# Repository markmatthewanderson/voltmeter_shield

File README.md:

# voltmeter_shield
 Voltmeter shield to be used with Arduino Uno.
 ....swag

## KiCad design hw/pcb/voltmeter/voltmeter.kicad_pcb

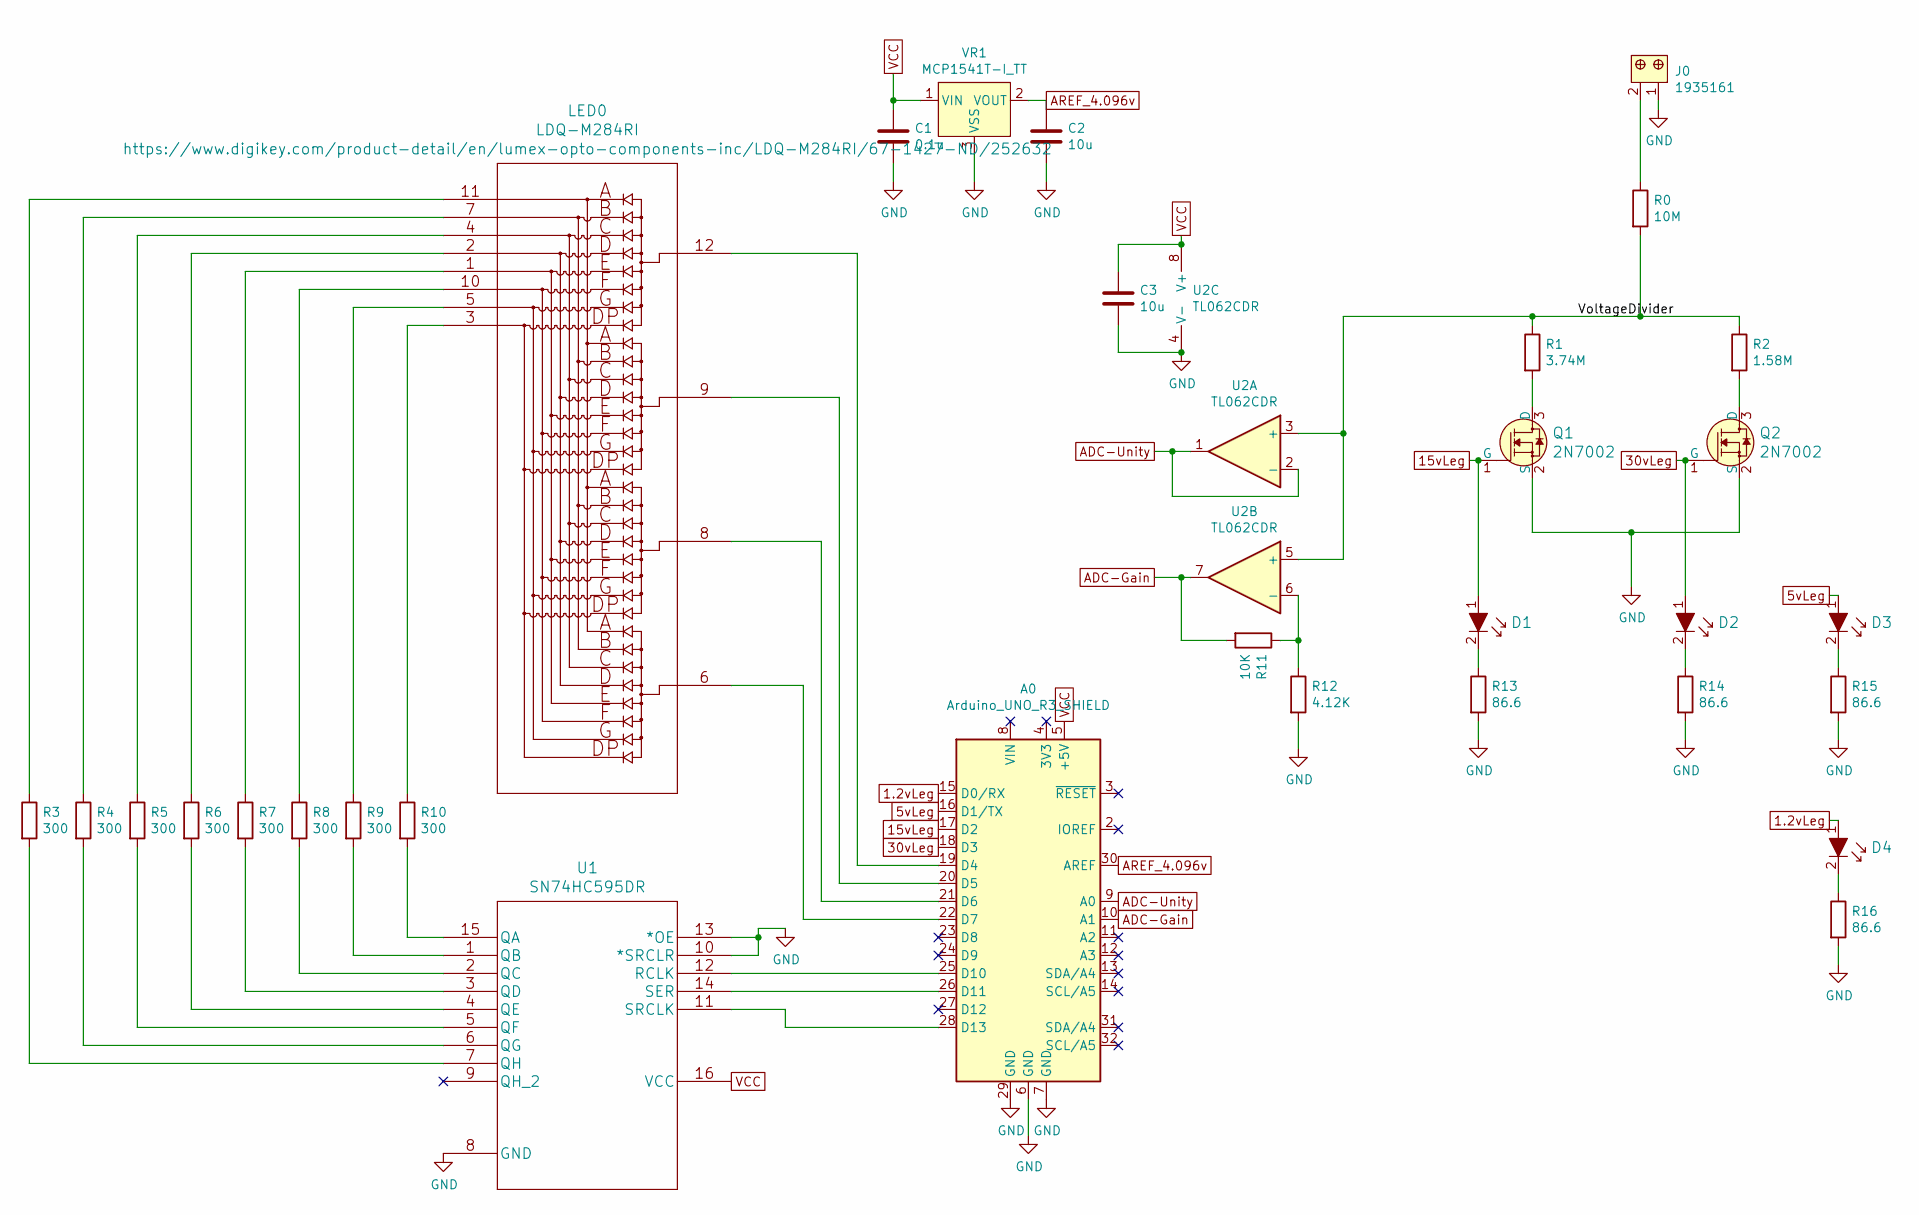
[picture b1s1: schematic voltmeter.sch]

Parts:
A0: Arduino_UNO_R3_SHIELD
C1: 0.1u; C_0805_2012Metric_Pad1.15x1.40mm_HandSolder
C2, C3: 10u; C_0805_2012Metric_Pad1.15x1.40mm_HandSolder
D1, D2, D3, D4: LTST-C150TBKT; 1206; MPN LTST-C150TBKT; Digi-Key_PN 160-1643-1-ND
J0: 1935161; Terminal_Block_D1.3mm_P5mm; MPN 1935161; Digi-Key_PN 277-1667-ND
LED0: LDQ-M284RI
Q1, Q2: 2N7002; SOT-23-3; MPN 2N7002; Digi-Key_PN 2N7002NCT-ND
R0: 10M; R_0805_2012Metric_Pad1.15x1.40mm_HandSolder
R1: 3.74M; R_0805_2012Metric_Pad1.15x1.40mm_HandSolder
R2: 1.58M; R_0805_2012Metric_Pad1.15x1.40mm_HandSolder
R3, R4, R5, R6, R7, R8, R9, R10: 300; R_0805_2012Metric_Pad1.15x1.40mm_HandSolder
R11: 10K; R_0805_2012Metric_Pad1.15x1.40mm_HandSolder
R12: 4.12K; R_0805_2012Metric_Pad1.15x1.40mm_HandSolder
R13, R14, R15, R16: 86.6; R_0805_2012Metric_Pad1.15x1.40mm_HandSolder
U1: SN74HC595DR
U2: TL062CDR
VR1: MCP1541T-I_TT; SOT-23-3; MPN MCP1541T-I/TT; Digi-Key_PN MCP1541T-I/TTCT-ND

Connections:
1.2vLeg: A0.15 (D0/RX), D4.1
5vLeg: A0.16 (D1/TX), D3.1
15vLeg: A0.17 (D2), D1.1, Q1.1 (G)
30vLeg: A0.18 (D3), D2.1, Q2.1 (G)
/VoltageDivider: R0.2, R1.1, R2.1, U2.3 (+), U2.5 (+)
ADC-Gain: A0.10 (A1), R11.2, U2.7
ADC-Unity: A0.9 (A0), U2.1, U2.2 (-)
AREF_4.096v: A0.30 (AREF), C2.1, VR1.2 (VOUT)
GND: A0.6 (GND), A0.7 (GND), A0.29 (GND), C1.2, C2.2, C3.2, J0.1, Q1.2 (S), Q2.2 (S), R12.2, R13.2, R14.2, R15.2, R16.2, U1.8 (GND), U1.10 (*SRCLR), U1.13 (*OE), U2.4 (V-), VR1.3 (VSS)
unnamed: A0.19 (D4), LED0.12
unnamed: A0.20 (D5), LED0.9
unnamed: A0.21 (D6), LED0.8
unnamed: A0.22 (D7), LED0.6
unnamed: A0.25 (D10), U1.12 (RCLK)
unnamed: A0.26 (D11), U1.14 (SER)
unnamed: A0.28 (D13), U1.11 (SRCLK)
unnamed: D1.2, R13.1
unnamed: D2.2, R14.1
unnamed: D3.2, R15.1
unnamed: D4.2, R16.1
unnamed: J0.2, R0.1
unnamed: LED0.1, R7.1
unnamed: LED0.2, R6.1
unnamed: LED0.3, R10.1
unnamed: LED0.4, R5.1
unnamed: LED0.5, R9.1
unnamed: LED0.7, R4.1
unnamed: LED0.10, R8.1
unnamed: LED0.11, R3.1
unnamed: Q1.3 (D), R1.2
unnamed: Q2.3 (D), R2.2
unnamed: R3.2, U1.7 (QH)
unnamed: R4.2, U1.6 (QG)
unnamed: R5.2, U1.5 (QF)
unnamed: R6.2, U1.4 (QE)
unnamed: R7.2, U1.3 (QD)
unnamed: R8.2, U1.2 (QC)
unnamed: R9.2, U1.1 (QB)
unnamed: R10.2, U1.15 (QA)
unnamed: R11.1, R12.1, U2.6 (-)
VCC: A0.5 (+5V), C1.1, C3.1, U1.16 (VCC), U2.8 (V+), VR1.1 (VIN)

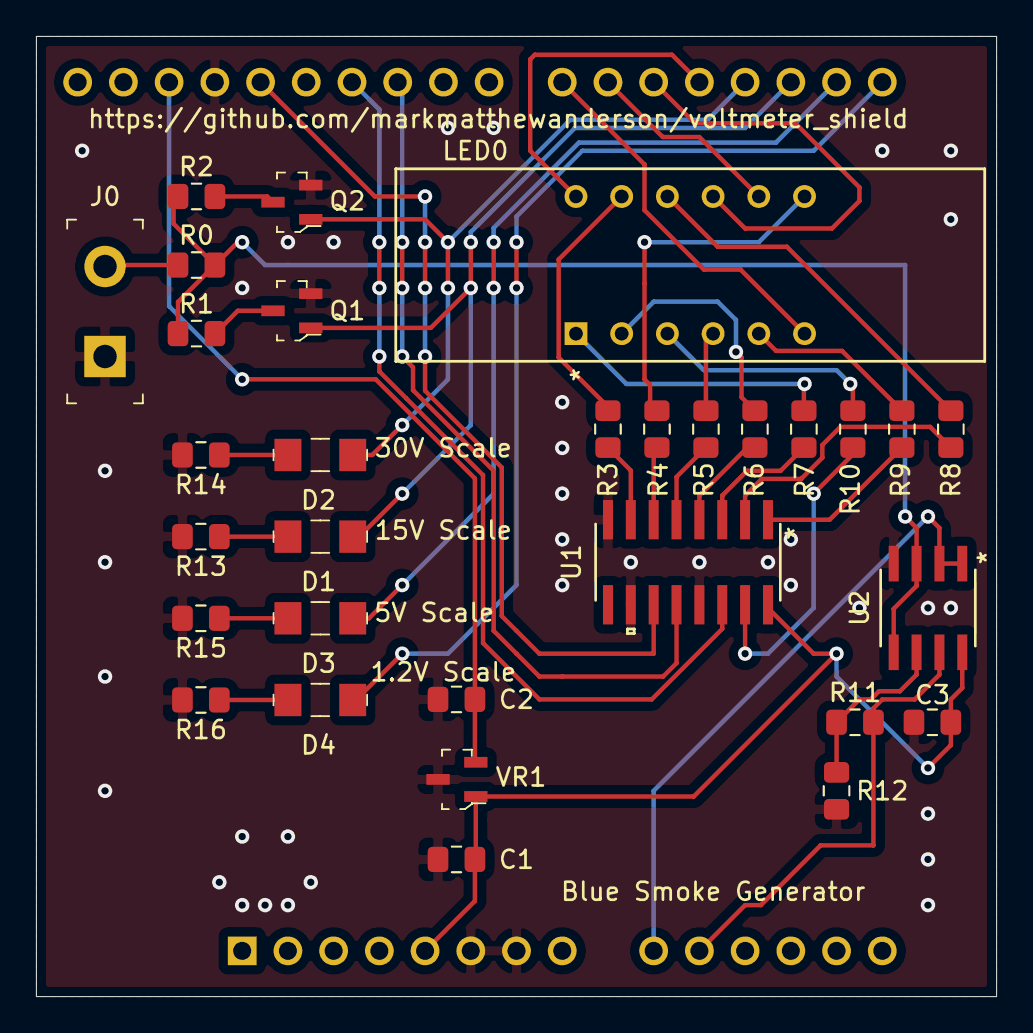
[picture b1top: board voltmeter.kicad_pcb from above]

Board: 2 copper layers, 53.3 x 53.3 mm, 32 parts (0 on the bottom side), 41 nets.

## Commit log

2020-08-21 Create folders & READMEs.
    Create folders for architecture, firmware, and hardware. Add READMEs for info/placeholders.
2020-08-21 Fix file extensions.
    Fix filenames of .txt files.
2020-08-21 Add blank Arduino and KiCAD projects.
    Created blank Arduino and KiCAD projects in their respective folders.
2020-08-21 Add architecture files.
    Begin drafting architecture information for firmware, hardware, and the system as a whole.
2020-08-21 Add ideas for voltage divider.
    Add resistor ideas for the voltage dividers for different voltage scales.
2020-08-22 Add ideas to arch, start schematic.
    Add ideas and details to architecture documents. Begin KiCAD circuit schematic and add to BOM.
2020-08-25 Test
    Test changes to demo Git client.
2020-08-25 Psuedo Code
    psuedo code
2020-08-26 Updated circuit, added components, demo PCB layout. w/ Adam
    Picked some parts and added them to the circuit. Implemented ADC circuit suggested by Nick.
2020-08-26 wolt
2020-08-26 Move to SMD parts; move to parts from Digikey library.
    Move to SMD parts; move to parts from Digikey library. Schematic updates.
2020-08-28 Psuedo Code
2020-08-28 Update
    update
2020-08-28 Changed to 4 voltage scales.
    Changed design from 3-scale to 4-scale. Selected a few more parts and added them to the schematic.
2020-08-28 Add Mac auto-generated file to .gitignore.
2020-08-31 Finished the schematic!
    Added 7-segment display, op-amps, and completed resistors and capacitors for ICs. First pass at the schematic is complete!
2020-09-01 Update voltmeter.ino
    Updated Psuedo Code
2020-09-01 Update voltmeter.ino
    psuedo code update
2020-09-02 Fix as many DRC errors as possible.
    Fixed DRC errors by marking unused pins and editing pin directionality on some schematic symbols.
2020-09-04 Begin PCB layout.
    Begin PCB layout. Edit Arduino footprint to better reflect the fact that it's just the header pins.
2020-09-17 Layout update.
    All components on the board. Saving a layout checkpoint for experimenting things.
2020-09-17 Finished the layout!
    Committing finalized layout.
2020-09-17 Generated gerber files.
    Generated gerber files. Beginning final component checks.
2020-09-17 Fix incorrect 7-segment pinout.
    Fixed bad 7-segment pinout. Fixed layout; regenerated gerbers.
2020-09-17 Added voltage scale labels to LEDs.
    Added voltage scale labels to LEDs. Regenerated gerber files.
2020-09-18 Add pin mapping to Arduino code.
    Added pin mapping to Arduino code with #define statements.
2020-09-20 Finalize board for order.
    Finalized BOM, saved BOM from DigiKey.
    Updated layout to match updated BOM.
2020-10-04 Schematic fix & updated Arduino pins.
    Fixed active low SRCLR pin on 595 shift register. Added test Arduino code. Fixed Arduino code pins.
2020-10-04 Update assembly_test.ino
    A little code clean up. Also experimented with enums (but commented it out).
2020-10-12 FW Update
2020-10-13 Tern
2020-10-13 Decimal
2020-10-13 counter
2020-10-13 ope_2
2020-10-20 Added test Arduino code file for Mark.
    Added test .ino Arduino code file for Mark to play with. File name is mma_test.ino.
2020-10-20 Add fudge factor and zero offset.

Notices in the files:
parts and their libraries:
Copyright 2016 Accelerated Designs. All rights reserved.
